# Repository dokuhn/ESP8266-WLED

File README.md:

# ESP8266-WLED

[![CC BY-NC-SA 4.0][cc-by-nc-sa-shield]][cc-by-nc-sa]

## Development Renderings

|  |   |
| :------: | :------: |
| Top | Bottom |

## License 

This work is licensed under a
[Creative Commons Attribution-NonCommercial-ShareAlike 4.0 International License][cc-by-nc-sa].

[![CC BY-NC-SA 4.0][cc-by-nc-sa-image]][cc-by-nc-sa]

[cc-by-nc-sa]: http://creativecommons.org/licenses/by-nc-sa/4.0/
[cc-by-nc-sa-image]: https://licensebuttons.net/l/by-nc-sa/4.0/88x31.png
[cc-by-nc-sa-shield]: https://img.shields.io/badge/License-CC%20BY--NC--SA%204.0-lightgrey.svg

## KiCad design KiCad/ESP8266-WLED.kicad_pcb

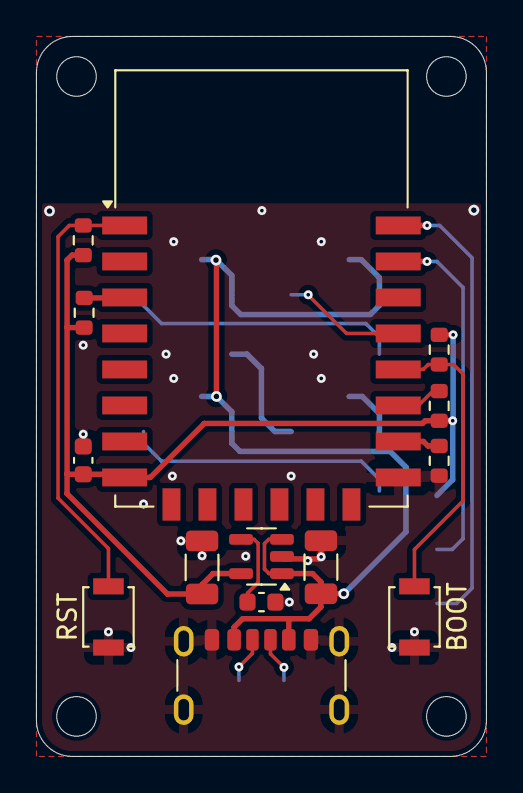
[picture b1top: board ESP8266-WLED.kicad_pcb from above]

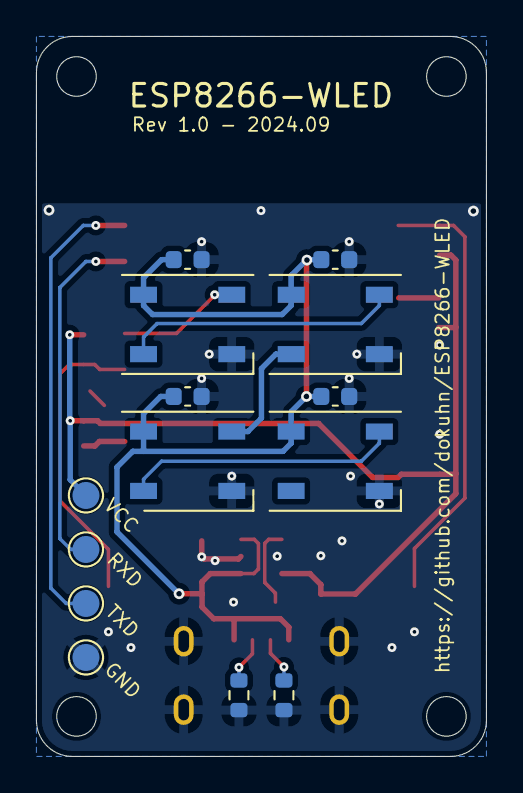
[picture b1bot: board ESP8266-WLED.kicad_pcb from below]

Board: 2 copper layers, 25.0 x 40.0 mm, 28 parts (14 on the bottom side), 17 nets.

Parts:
C1, C2, C3, C4, C5: 100nF; C_0603_1608Metric
C6, C7: 10u; C_1206_3216Metric
C8: 470pF; C_0603_1608Metric
D1, D2, D3, D4: WS2812B; LED_WS2812B_PLCC4_5.0x5.0mm_P3.2mm
J1: USB_C_Receptacle_USB2.0_14P; USB_C_Receptacle_GCT_USB4125-xx-x-0190_6P_TopMnt_Horizontal
J2, J3, J4, J5: Conn_01x01_Socket; TestPoint_Pad_D1.5mm
R1, R2, R3, R4, R5: 10K; R_0603_1608Metric
R6, R7: 5k1; R_0603_1608Metric
SW1, SW2: SW_Push; SW_SPST_B3U-1000P
U1: ESP-12F; ESP-12E
U2: MIC5219-3.3YM5; SOT-23-5

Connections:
+3V3: C1.1, C7.1, J2.1, R1.1, R2.1, R3.1, R4.1, U1.8 (VCC), U2.5 (OUT)
+5V: C2.1, C3.1, C4.1, C5.1, C6.1, D1.1 (VDD), D2.1 (VDD), D3.1 (VDD), D4.1 (VDD), J1.A9 (VBUS), J1.B9 (VBUS), U2.1 (IN), U2.3 (EN)
/DIN: D1.4 (DIN), U1.19 (GPIO4)
/RXD: J3.1, U1.21 (GPIO3/RXD)
/TXD: J4.1, U1.22 (GPIO1/TXD)
GND: C1.2, C2.2, C3.2, C4.2, C5.2, C6.2, C7.2, C8.2, D1.3 (VSS), D2.3 (VSS), D3.3 (VSS), D4.3 (VSS), J1.A12 (GND), J1.B12 (GND), J1.S1 (SHIELD), J5.1, R5.2, R6.2, R7.2, SW1.1, SW2.1, U1.15 (GND), U2.2 (GND)
unnamed: D1.2 (DOUT), D2.4 (DIN)
unnamed: D2.2 (DOUT), D3.4 (DIN)
unnamed: D3.2 (DOUT), D4.4 (DIN)
unnamed: J1.A5 (CC1), R6.1
unnamed: J1.B5 (CC2), R7.1
unnamed: R2.2, U1.3 (EN)
unnamed: R3.2, SW1.2, U1.18 (GPIO0)
unnamed: R4.2, U1.17 (GPIO2)
unnamed: R5.1, U1.16 (GPIO15)
unnamed: R1.2, SW2.2, U1.1 (~RST)
unnamed: C8.1, U2.4 (BP)

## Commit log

2024-09-28 adding KiCad files
2024-09-29 adding power supply, etc.
2024-09-29 adding serial interface
2024-09-30 updating README file
2024-10-01 First time finalizing the schematic and fixing all errors
2024-10-03 first placement
2024-10-07 first traces routed
2024-10-07 first time everything routed
2024-10-08 making some fine-tuning of the PCB
2024-10-09 adding LCSC parts
